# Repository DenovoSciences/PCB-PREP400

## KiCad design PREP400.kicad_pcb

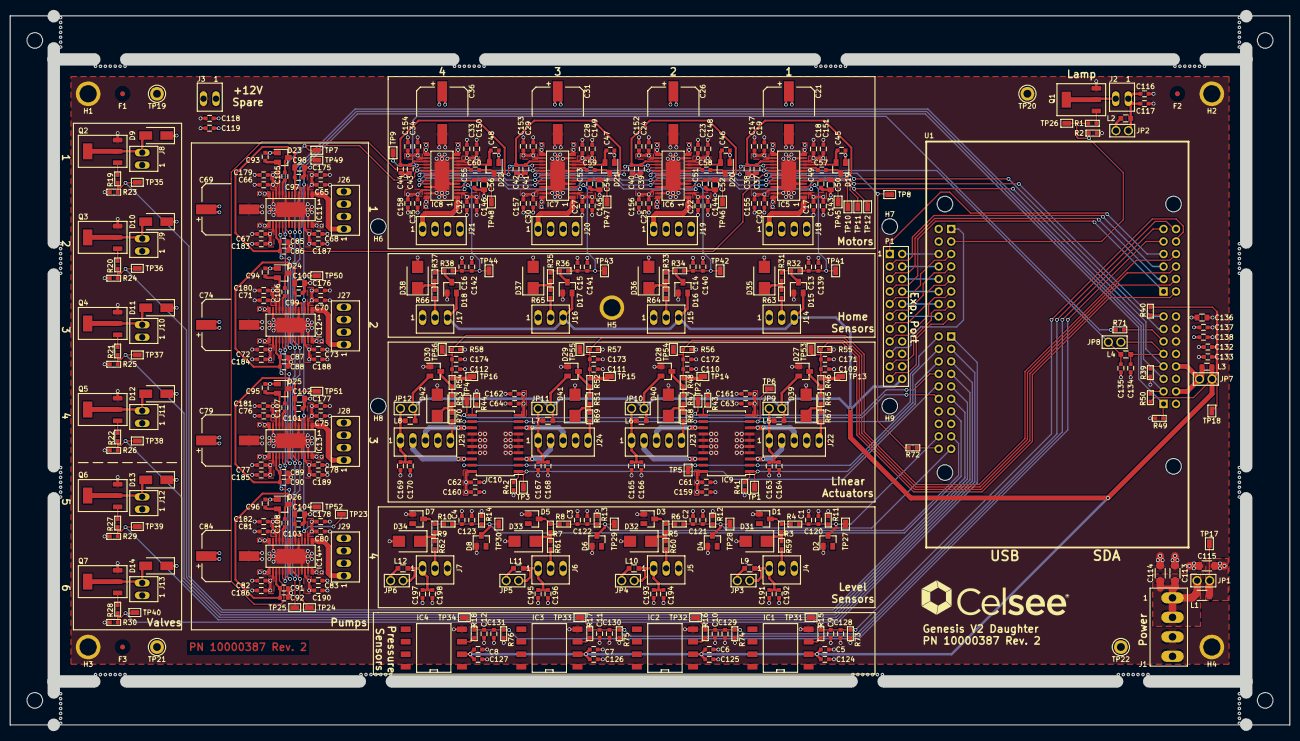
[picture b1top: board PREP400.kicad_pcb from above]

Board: 4 copper layers, 260.2 x 144.2 mm, 467 parts (0 on the bottom side), 204 nets.

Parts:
C1, C2, C3, C4, C5, C6, C7, C8, C9, C10, C11, C12, C13, C14, C15, C16, C17, C18, C19, C20, C22, C23, C24, C25, C27, C28, C29, C30, C32, C33, C34, C35, C37, C39, C41, C43, C49, C51, C53, C55, C61, C62, C63, C64, C65, C66, C67, C68, C70, C71, C72, C73, C75, C76, C77, C78, C80, C81, C82, C83, C85, C87, C89, C91, C97, C99, C101, C103, C109, C110, C111, C112, C137: 100nF/50V; CAP_SMD_0603
C21, C26, C31, C36, C69, C74, C79, C84: 100uF/50V; CAP_SMD_RAD_10MM
C38, C40, C42, C44, C86, C88, C90, C92: 10uF/6V3; CAP_SMD_0603
C45, C46, C47, C48, C93, C94, C95, C96: 220nF/50V; CAP_SMD_0603
C50, C52, C54, C56, C98, C100, C102, C104: 47uF/6V3; CAP_SMD_0805
C57, C58, C59, C60, C105, C106, C107, C108, C120, C121, C122, C123, C124, C125, C126, C127, C128, C129, C130, C131, C138, C139, C140, C141, C142, C143, C144, C145, C146, C147, C148, C149, C150, C151, C152, C153, C154, C155, C156, C157, C158, C159, C160, C161, C162, C171, C172, C173, C174, C175, C176, C177, C178, C179, C180, C181, C182, C183, C184, C185, C186, C187, C188, C189, C190: 10nF/50V; CAP_SMD_0603
C113: 100nF/50V; CAP_SMD_1206
C114: 10nF/50V; CAP_SMD_1206
C115: 1206; CAP_SMD_1206
C116, C117, C118, C119, C132, C133, C134, C135, C163, C164, C165, C166, C167, C168, C169, C170, C191, C192, C193, C194, C195, C196, C197, C198: 0603; CAP_SMD_0603
C136: 0805; CAP_SMD_0805
D1, D3, D5, D7: BAT54; SOT-23-3
D2, D4, D6, D8: BZX84; SOT-23-3
D9, D10, D11, D12, D13, D14: 100V@1A; SMA
D15, D16, D17, D18, D27, D28, D29, D30: BAT54S; SOT-23-3
D19, D20, D21, D22, D23, D24, D25, D26: BAV99; SOT-23-3
D31, D32, D33, D34, D35, D36, D37, D38, D39, D40, D41, D42: SMB
F1, F2, F3: VAL**; FID_BTM_1MM
F1#2, F2#2, F3#2: VAL**; FID_TOP_1MM
H1, H2, H3, H4, H5: VAL**; MNT_3.5MM
H6, H7, H8, H9, H10, H11, H12, H13: VAL**; MNT_0.125IN
IC1, IC2, IC3, IC4: SSC; SMT-8
IC5, IC6, IC7, IC8, IC11, IC12, IC13, IC14: L6472; HTSSOP-28
IC9, IC10: L293DD; SOIC-20
J1: MTA04-156; CON_AMP_MTA156_1x4
J2, J3, J8, J9, J10, J11, J12, J13: MTA02-100; CON_AMP_MTA100_1x2
J4, J5, J6, J7, J14, J15, J16, J17: MTA03-100; CON_AMP_MTA100_1x3
J18, J19, J20, J21, J26, J27, J28, J29: MTA04-100; CON_AMP_MTA100_1x4
J22, J23, J24, J25: MTA05-100; CON_AMP_MTA100_1x5
JP1: jump_no; CON_JMP_100_1x2
JP2, JP3, JP4, JP5, JP6, JP7, JP8, JP9, JP10, JP11, JP12: jump_nc; CON_JMP_100_1x2
L1: 1206; FER_SMD_1206
L2, L3, L4, L5, L6, L7, L8, L9, L10, L11, L12: 0805; FER_SMD_0805
P1: CONN_EXP2; CON_SAMTEC_100_2x11
Q1, Q2, Q3, Q4, Q5, Q6, Q7: FQT13N06L; SOT_223
R1, R19, R20, R21, R22, R27, R28: 330; RES_SMD_0603
R2, R23, R24, R25, R26, R29, R30, R39, R41, R42, R43, R44, R49: 10k; RES_SMD_0603
R3, R5, R7, R9, R31, R33, R35, R37, R45, R47, R51, R53, R59, R60, R61, R62, R63, R64, R65, R66, R67, R68, R69, R70: 100; RES_SMD_0603
R4, R6, R8, R10: 1.5k; RES_SMD_0603
R11, R12, R13, R14, R55, R56, R57, R58, R73, R74, R75, R76: 100k; RES_SMD_0603
R15, R16, R17, R18, R32, R34, R36, R38, R46, R48, R52, R54: 1k; RES_SMD_0603
R40, R50: 39k; RES_SMD_0603
R71, R72: 0; RES_SMD_0603
TP1, TP2, TP3, TP4, TP5, TP6, TP7, TP8, TP9, TP10, TP11, TP12, TP13, TP14, TP15, TP16, TP17, TP18, TP23, TP24, TP25, TP26, TP27, TP28, TP29, TP30, TP31, TP32, TP33, TP34, TP35, TP36, TP37, TP38, TP39, TP40, TP41, TP42, TP43, TP44, TP45, TP46, TP47, TP48, TP49, TP50, TP51, TP52, TP53, TP54, TP55, TP56: TP; TP_SMD_0603
TP19, TP20, TP21, TP22: TP; Test_Point_Keystone_5005-5009_Compact
U1: FRDM-KL25Z

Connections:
+3V3: C5.1, C6.1, C7.1, C8.1, C124.1, C125.1, C126.1, C127.1, C132.1, C133.1, D15.2, D16.2, D17.2, D18.2, D27.2, D28.2, D29.2, D30.2, IC1.2, IC2.2, IC3.2, IC4.2, J14.3, J15.3, J16.3, J17.3, JP7.2, JP9.2, JP10.2, JP11.2, JP12.2, L3.2, L5.2, L6.2, L7.2, L8.2, P1.22, R40.2, R50.2, TP18.1
+12V: C17.1, C18.1, C19.1, C20.1, C21.1, C22.1, C23.1, C24.1, C25.1, C26.1, C27.1, C28.1, C29.1, C30.1, C31.1, C32.1, C33.1, C34.1, C35.1, C36.1, C45.1, C46.1, C47.1, C48.1, C61.2, C62.2, C63.1, C64.1, C65.1, C66.1, C67.1, C68.1, C69.1, C70.1, C71.1, C72.1, C73.1, C74.1, C75.1, C76.1, C77.1, C78.1, C79.1, C80.1, C81.1, C82.1, C83.1, C84.1, C93.1, C94.1, C95.1, C96.1, C115.1, C118.1, C119.1, C136.1, C137.1, C138.1, C143.1, C144.1, C145.1, C146.1, C147.1, C148.1, C149.1, C150.1, C151.1, C152.1, C153.1, C154.1, C155.1, C156.1, C157.1, C158.1, C159.2, C160.2, C161.1, C162.1, C175.1, C176.1, C177.1, C178.1, C179.1, C180.1, C181.1, C182.1, C183.1, C184.1, C185.1, C186.1, C187.1, C188.1, C189.1, C190.1, D9.1, D10.1, D11.1, D12.1, D13.1, D14.1, D19.1, D20.1, D21.1, D22.1, D23.1, D24.1, D25.1, D26.1, IC5.2, IC5.12, IC5.16, IC5.26, IC6.2, IC6.12, IC6.16, IC6.26, IC7.2, IC7.12, IC7.16, IC7.26, IC8.2, IC8.12, IC8.16, IC8.26, IC9.10, IC9.20, IC10.10, IC10.20, IC11.2, IC11.12, IC11.16, IC11.26, IC12.2, IC12.12, IC12.16, IC12.26, IC13.2, IC13.12, IC13.16, IC13.26, IC14.2, IC14.12, IC14.16, IC14.26, J3.1, J8.1, J9.1, J10.1, J11.1, J12.1, J13.1, JP1.2, JP2.1, JP3.1, JP4.1, JP5.1, JP6.1, L1.2, L2.2, L9.1, L10.1, L11.1, L12.1, P1.14, P1.16, TP17.1, U1.4-16
/LinearActuator/LIN_OUT1A: IC9.3, J22.2
/LinearActuator/LIN_OUT1B: IC9.8, J22.3
/LinearActuator/LIN_OUT2A: IC9.18, J23.2
/LinearActuator/LIN_OUT2B: IC9.13, J23.3
/LinearActuator/LIN_OUT3A: IC10.3, J24.2
/LinearActuator/LIN_OUT3B: IC10.8, J24.3
/LinearActuator/LIN_OUT4A: IC10.18, J25.2
/LinearActuator/LIN_OUT4B: IC10.13, J25.3
/Microcontroller/EXP_A0: P1.1, U1.3-7
/Microcontroller/EXP_A1: P1.3, U1.3-5
/Microcontroller/EXP_A2: P1.5, U1.3-3
/Microcontroller/EXP_A3: P1.7, U1.3-1
/Microcontroller/EXP_D0: P1.9, U1.1-5
/Microcontroller/EXP_D1_SPI0_CS: P1.11, U1.1-7
/Microcontroller/EXP_D2_SPI0_SCK: P1.13, U1.1-9
/Microcontroller/EXP_D3_SPI0_MOSI: P1.15, U1.1-11
/Microcontroller/EXP_D4_SPI0_MISO: P1.17, U1.1-1
/Microcontroller/EXP_D5_I2C1_SCL: P1.19, U1.1-13
/Microcontroller/EXP_D6_I2C1_SDA: P1.21, U1.1-15
/Microcontroller/EXP_D7: P1.12, U1.1-16
/Microcontroller/EXP_D8: P1.10, U1.1-14
/Microcontroller/EXP_D9: P1.8, U1.1-12
/Microcontroller/EXP_D10: P1.6, U1.1-10
/Microcontroller/EXP_D11: P1.4, U1.1-8
/Microcontroller/EXP_D12: P1.2, U1.1-6
/Microcontroller/LAMP: R1.2, R2.1, TP26.1, U1.1-3
/Microcontroller/LEVEL1: C1.1, C120.1, D2.3, R4.1, R11.1, TP27.1, U1.2-18
/Microcontroller/LEVEL2: C2.1, C121.1, D4.3, R6.1, R12.1, TP28.1, U1.2-19
/Microcontroller/LEVEL3: C3.1, C122.1, D6.3, R8.1, R13.1, TP29.1, U1.2-17
/Microcontroller/LEVEL4: C4.1, C123.1, D8.3, R10.1, R14.1, TP30.1, U1.2-13
/Microcontroller/LIN_ACT_DIR: IC9.2, IC9.19, IC10.2, IC10.19, TP5.1, U1.2-4
/Microcontroller/LIN_ACT_EN1: IC9.1, R41.1, TP1.1, U1.2-6
/Microcontroller/LIN_ACT_EN2: IC9.11, R43.2, TP2.1, U1.2-8
/Microcontroller/LIN_ACT_EN3: IC10.1, R42.1, TP3.1, U1.2-10
/Microcontroller/LIN_ACT_EN4: IC10.11, R44.2, TP4.1, U1.2-12
/Microcontroller/LIN_ACT_POS1: C109.1, C171.1, R46.2, R55.1, TP13.1, TP53.1, U1.3-2
/Microcontroller/LIN_ACT_POS2: C110.1, C172.1, R48.2, R56.1, TP14.1, TP54.1, U1.3-4
/Microcontroller/LIN_ACT_POS3: C111.1, C173.1, R52.2, R57.1, TP15.1, TP55.1, U1.3-6
/Microcontroller/LIN_ACT_POS4: C112.1, C174.1, R54.2, R58.1, TP16.1, TP56.1, U1.3-8
/Microcontroller/PRESSURE1: C9.1, C128.1, R15.1, R73.1, TP31.1, U1.3-10
/Microcontroller/PRESSURE2: C10.1, C129.1, R16.1, R74.1, TP32.1, U1.3-12
/Microcontroller/PRESSURE3: C11.1, C130.1, R17.1, R75.1, TP33.1, U1.3-11
/Microcontroller/PRESSURE4: C12.1, C131.1, R18.1, R76.1, TP34.1, U1.3-9
/Microcontroller/VALVE1: R19.2, R23.1, TP35.1, U1.2-11
/Microcontroller/VALVE2: R20.2, R24.1, TP36.1, U1.2-9
/Microcontroller/VALVE3: R21.2, R25.1, TP37.1, U1.2-7
/Microcontroller/VALVE4: R22.2, R26.1, TP38.1, U1.2-5
/Microcontroller/VALVE5: R27.2, R29.1, TP39.1, U1.2-3
/Microcontroller/VALVE6: R28.2, R30.1, TP40.1, U1.2-1
/Microcontroller/_LIN_ACT_DIR: IC9.9, IC9.12, IC10.9, IC10.12, TP6.1, U1.2-2
/Motor/MOT1_1A: IC5.1, J18.1
/Motor/MOT1_1B: IC5.14, J18.4
/Motor/MOT1_2A: IC5.28, J18.2
/Motor/MOT1_2B: IC5.15, J18.3
/Motor/MOT1_HOME: C13.1, C139.1, IC5.4, R32.2, TP41.1
/Motor/MOT2_1A: IC6.1, J19.1
/Motor/MOT2_1B: IC6.14, J19.4
/Motor/MOT2_2A: IC6.28, J19.2
/Motor/MOT2_2B: IC6.15, J19.3
/Motor/MOT2_HOME: C14.1, C140.1, IC6.4, R34.2, TP42.1
/Motor/MOT3_1A: IC7.1, J20.1
/Motor/MOT3_1B: IC7.14, J20.4
/Motor/MOT3_2A: IC7.28, J20.2
/Motor/MOT3_2B: IC7.15, J20.3
/Motor/MOT3_HOME: C15.1, C141.1, IC7.4, R36.2, TP43.1
/Motor/MOT4_1A: IC8.1, J21.1
/Motor/MOT4_1B: IC8.14, J21.4
/Motor/MOT4_2A: IC8.28, J21.2
/Motor/MOT4_2B: IC8.15, J21.3
/Motor/MOT4_HOME: C16.1, C142.1, IC8.4, R38.2, TP44.1
/Motor/MOT_SCK: C135.1, IC5.19, IC6.19, IC7.19, IC8.19, IC11.19, IC12.19, IC13.19, IC14.19, JP8.2, L4.2, TP7.1
/Motor/MOT_SDI: IC5.20, IC11.20, R72.2, TP8.1
/Motor/MOT_SDO: IC8.18, IC14.18, R71.1, TP9.1
/Motor/_MOTC_CS: IC5.23, IC6.23, IC7.23, IC8.23, TP10.1, U1.4-13
/Motor/_MOTC_FLG: IC5.24, IC6.24, IC7.24, IC8.24, R40.1, TP11.1, U1.4-15
/Motor/_MOTC_RST: IC5.3, IC6.3, IC7.3, IC8.3, R39.2, TP12.1, U1.4-7
/Pump/MOT1_1A: IC11.1, J26.1
/Pump/MOT1_1B: IC11.14, J26.4
/Pump/MOT1_2A: IC11.28, J26.2
/Pump/MOT1_2B: IC11.15, J26.3
/Pump/MOT1_VDD: C85.1, C86.1, C97.1, C98.1, IC11.4, IC11.6, IC11.17, TP49.1
/Pump/MOT2_1A: IC12.1, J27.1
/Pump/MOT2_1B: IC12.14, J27.4
/Pump/MOT2_2A: IC12.28, J27.2
/Pump/MOT2_2B: IC12.15, J27.3
/Pump/MOT2_VDD: C87.1, C88.1, C99.1, C100.1, IC12.4, IC12.6, IC12.17, TP50.1
/Pump/MOT3_1A: IC13.1, J28.1
/Pump/MOT3_1B: IC13.14, J28.4
/Pump/MOT3_2A: IC13.28, J28.2
/Pump/MOT3_2B: IC13.15, J28.3
/Pump/MOT3_VDD: C89.1, C90.1, C101.1, C102.1, IC13.4, IC13.6, IC13.17, TP51.1
/Pump/MOT4_1A: IC14.1, J29.1
/Pump/MOT4_1B: IC14.14, J29.4
/Pump/MOT4_2A: IC14.28, J29.2
/Pump/MOT4_2B: IC14.15, J29.3
/Pump/MOT4_VDD: C91.1, C92.1, C103.1, C104.1, IC14.4, IC14.6, IC14.17, TP52.1
/Pump/_MOTP_CS: IC11.23, IC12.23, IC13.23, IC14.23, TP25.1, U1.4-5
/Pump/_MOTP_FLG: IC11.24, IC12.24, IC13.24, IC14.24, R50.1, TP24.1, U1.4-3
/Pump/_MOTP_RST: IC11.3, IC12.3, IC13.3, IC14.3, R49.2, TP23.1, U1.4-1
GND: C1.2, C2.2, C3.2, C4.2, C5.2, C6.2, C7.2, C8.2, C9.2, C10.2, C11.2, C12.2, C13.2, C14.2, C15.2, C16.2, C17.2, C18.2, C19.2, C20.2, C21.2, C22.2, C23.2, C24.2, C25.2, C26.2, C27.2, C28.2, C29.2, C30.2, C31.2, C32.2, C33.2, C34.2, C35.2, C36.2, C37.2, C38.2, C39.2, C40.2, C41.2, C42.2, C43.2, C44.2, C49.2, C50.2, C51.2, C52.2, C53.2, C54.2, C55.2, C56.2, C61.1, C62.1, C63.2, C64.2, C65.2, C66.2, C67.2, C68.2, C69.2, C70.2, C71.2, C72.2, C73.2, C74.2, C75.2, C76.2, C77.2, C78.2, C79.2, C80.2, C81.2, C82.2, C83.2, C84.2, C85.2, C86.2, C87.2, C88.2, C89.2, C90.2, C91.2, C92.2, C97.2, C98.2, C99.2, C100.2, C101.2, C102.2, C103.2, C104.2, C109.2, C110.2, C111.2, C112.2, C113.2, C114.2, C115.2, C116.2, C117.2, C118.2, C119.2, C120.2, C121.2, C122.2, C123.2, C124.2, C125.2, C126.2, C127.2, C128.2, C129.2, C130.2, C131.2, C132.2, C133.2, C134.2, C135.2, C136.2, C137.2, C138.2, C139.2, C140.2, C141.2, C142.2, C143.2, C144.2, C145.2, C146.2, C147.2, C148.2, C149.2, C150.2, C151.2, C152.2, C153.2, C154.2, C155.2, C156.2, C157.2, C158.2, C159.1, C160.1, C161.2, C162.2, C163.1, C164.1, C165.1, C166.1, C167.1, C168.1, C169.1, C170.1, C171.2, C172.2, C173.2, C174.2, C175.2, C176.2, C177.2, C178.2, C179.2, C180.2, C181.2, C182.2, C183.2, C184.2, C185.2, C186.2, C187.2, C188.2, C189.2, C190.2, C191.1, C192.1, C193.1, C194.1, C195.1, C196.1, C197.1, C198.1, D1.1, D2.1, D3.1, D4.1, D5.1, D6.1, D7.1, D8.1, D15.1, D16.1, D17.1, D18.1, D27.1, D28.1, D29.1, D30.1, D31.2, D32.2, D33.2, D34.2, D35.2, D36.2, D37.2, D38.2, D39.2, D40.2, D41.2, D42.2, H1.1, H2.1, H3.1, H4.1, H5.1, IC1.4, IC2.4, IC3.4, IC4.4, IC5.5, IC5.9, IC5.13, IC5.21, IC5.25, IC5.27, IC5.29, IC6.5, IC6.9, IC6.13, IC6.21, IC6.25, IC6.27, IC6.29, IC7.5, IC7.9, IC7.13, IC7.21, IC7.25, IC7.27, IC7.29, IC8.5, IC8.9, IC8.13, IC8.21, IC8.25, IC8.27, IC8.29, IC9.4, IC9.5, IC9.6, IC9.7, IC9.14, IC9.15, IC9.16, IC9.17, IC10.4, IC10.5, IC10.6, IC10.7, IC10.14, IC10.15, IC10.16, IC10.17, IC11.5, IC11.9, IC11.13, IC11.21, IC11.25, IC11.27, IC11.29, IC12.5, IC12.9, IC12.13, IC12.21, IC12.25, IC12.27, IC12.29, IC13.5, IC13.9, IC13.13, IC13.21, IC13.25, IC13.27, IC13.29, IC14.5, IC14.9, IC14.13, IC14.21, IC14.25, IC14.27, IC14.29, J1.3, J1.4, J3.2, J4.3, J5.3, J6.3, J7.3, J14.1, J15.1, J16.1, J17.1, J22.4, J23.4, J24.4, J25.4, P1.18, P1.20, Q1.S, Q2.S, Q3.S, Q4.S, Q5.S, Q6.S, Q7.S, R2.2, R11.2, R12.2, R13.2, R14.2, R23.2, R24.2, R25.2, R26.2, R29.2, R30.2, R39.1, R41.2, R42.2, R43.1, R44.1, R49.1, R55.2, R56.2, R57.2, R58.2, R73.2, R74.2, R75.2, R76.2, TP19.1, TP20.1, TP21.1, TP22.1, U1.2-14, U1.4-12, U1.4-14
unnamed: C37.1, C38.1, C49.1, C50.1, IC5.6, IC5.17, TP45.1
unnamed: C39.1, C40.1, C51.1, C52.1, IC6.6, IC6.17, TP46.1
unnamed: C41.1, C42.1, C53.1, C54.1, IC7.6, IC7.17, TP47.1
unnamed: C43.1, C44.1, C55.1, C56.1, IC8.6, IC8.17, TP48.1
unnamed: C45.2, D19.2, IC5.11
unnamed: C46.2, D20.2, IC6.11
unnamed: C47.2, D21.2, IC7.11
unnamed: C48.2, D22.2, IC8.11
unnamed: C57.1, D19.3
unnamed: C57.2, IC5.10
unnamed: C58.1, D20.3
unnamed: C58.2, IC6.10
unnamed: C59.1, D21.3
unnamed: C59.2, IC7.10
unnamed: C60.1, D22.3
unnamed: C60.2, IC8.10
unnamed: C93.2, D23.2, IC11.11
unnamed: C94.2, D24.2, IC12.11
unnamed: C95.2, D25.2, IC13.11
unnamed: C96.2, D26.2, IC14.11
unnamed: C105.1, D23.3
unnamed: C105.2, IC11.10
unnamed: C106.1, D24.3
unnamed: C106.2, IC12.10
unnamed: C107.1, D25.3
unnamed: C107.2, IC13.10
unnamed: C108.1, D26.3
unnamed: C108.2, IC14.10
unnamed: C113.1, C114.1, J1.1, J1.2, JP1.1, L1.1
unnamed: C116.1, C117.1, J2.1, JP2.2, L2.1
unnamed: C134.1, JP8.1, L4.1, U1.4-9
unnamed: C163.2, C164.2, J22.1, JP9.1, L5.1
unnamed: C165.2, C166.2, J23.1, JP10.1, L6.1
unnamed: C167.2, C168.2, J24.1, JP11.1, L7.1
unnamed: C169.2, C170.2, J25.1, JP12.1, L8.1
unnamed: C191.2, C192.2, J4.1, JP3.2, L9.2
unnamed: C193.2, C194.2, J5.1, JP4.2, L10.2
unnamed: C195.2, C196.2, J6.1, JP5.2, L11.2
unnamed: C197.2, C198.2, J7.1, JP6.2, L12.2
unnamed: D1.3, R3.1, R4.2
unnamed: D3.3, R5.1, R6.2
unnamed: D5.3, R7.1, R8.2
unnamed: D7.3, R9.1, R10.2
unnamed: D9.2, J8.2, Q2.D
unnamed: D10.2, J9.2, Q3.D
unnamed: D11.2, J10.2, Q4.D
unnamed: D12.2, J11.2, Q5.D
unnamed: D13.2, J12.2, Q6.D
unnamed: D14.2, J13.2, Q7.D
unnamed: D15.3, R31.2, R32.1
unnamed: D16.3, R33.2, R34.1
unnamed: D17.3, R35.2, R36.1
unnamed: D18.3, R37.2, R38.1
unnamed: D27.3, R45.2, R46.1
unnamed: D28.3, R47.2, R48.1
unnamed: D29.3, R51.2, R52.1
unnamed: D30.3, R53.2, R54.1
unnamed: D31.1, R3.2, R59.1
unnamed: D32.1, R5.2, R60.1
unnamed: D33.1, R7.2, R61.1
unnamed: D34.1, R9.2, R62.1
unnamed: D35.1, R31.1, R63.2
unnamed: D36.1, R33.1, R64.2
unnamed: D37.1, R35.1, R65.2
unnamed: D38.1, R37.1, R66.2
unnamed: D39.1, R45.1, R67.2
unnamed: D40.1, R47.1, R68.2
unnamed: D41.1, R51.1, R69.2
unnamed: D42.1, R53.1, R70.2
unnamed: IC1.3, R15.2
unnamed: IC2.3, R16.2
unnamed: IC3.3, R17.2
unnamed: IC4.3, R18.2
unnamed: IC5.18, IC6.20
unnamed: IC6.18, IC7.20
unnamed: IC7.18, IC8.20
unnamed: IC11.18, IC12.20
unnamed: IC12.18, IC13.20
unnamed: IC13.18, IC14.20
unnamed: J2.2, Q1.D
unnamed: J4.2, R59.2
unnamed: J5.2, R60.2
unnamed: J6.2, R61.2
unnamed: J7.2, R62.2
unnamed: J14.2, R63.1
unnamed: J15.2, R64.1
unnamed: J16.2, R65.1
unnamed: J17.2, R66.1
unnamed: J22.5, R67.1
unnamed: J23.5, R68.1
unnamed: J24.5, R69.1
unnamed: J25.5, R70.1
unnamed: JP7.1, L3.1, U1.4-4, U1.4-8
unnamed: Q1.G, R1.1
unnamed: Q2.G, R19.1
unnamed: Q3.G, R20.1
unnamed: Q4.G, R21.1
unnamed: Q5.G, R22.1
unnamed: Q6.G, R27.1
unnamed: Q7.G, R28.1
unnamed: R71.2, U1.4-11
unnamed: R72.1, U1.2-20

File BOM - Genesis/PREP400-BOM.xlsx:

References | Quantity | Description | Mfg | MfgPartNum | DigikeyPartNum | AltDigikeyPartNum | Notes
C1, C2, C3, C4, C5, C6, C7, C8, C9, C10, C11, C12, C13, C14, C15, C16, C17, C18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 | 84 | CAP CER 0.1UF 50V X7R 0603 | Murata | GCM188R71H104KA57J | 490-8020-1-ND |  | Do Not Populate: C116, C132, C163, C165, C167, C169, C191, C193, C195, C197
C113 | 1 | CAP CER 0.1UF 100V X7R 1206 | Kemet | C1206C104K1RACAUTO | 399-7008-1-ND | 445-5840-1-ND | Do Not Populate: C113
C21, C26, C31, C36, C69, C74, C79, C84 | 8 | CAP ALUM POLY 100UF 20% 50V SMD | Panasonic | EEH-ZC1H101V | P19837CT-ND | 50PFV100M10X10.5CT-ND
C38, C40, C42, C44, C86, C88, C90, C92 | 8 | CAP CER 10UF 10V X5R 0603 | TDK | C1608X5R1A106K080AC | 445-7486-1-ND | 1276-1038-1-ND
C45, C46, C47, C48, C93, C94, C95, C96 | 8 | CAP CER 0.22UF 50V X7R 0603 | Samsung | CL10B224KB8VPNC | 1276-6600-1-ND
C50, C52, C54, C56, C98, C100, C102, C104, C136 | 9 | CAP CER 47UF 6.3V X5R 0805 | Samsung | CL21A476MQ9LRNC | 1276-2419-1-ND |  | Do Not Populate: C136
C115 | 1 | CAP CER 47UF 6.3V X5R 1206 | Samsung | CL31A476KQHNNNE | 1276-3062-1-ND |  | Do Not Populate: C115
C57, C58, C59, C60, C105, C106, C107, C108, C117, C119, C120, C121, C122, C123,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 | 77 | CAP CER 10000PF 50V X7R 0603 | Murata | GCM188R71H103KA37D | 490-4778-1-ND |  | Do Not Populate: C117, C133, C134, C164, C166, C168, C170, C192, C194, C196, C1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
C114 | 1 | CAP CER 10000PF 200V X7R 1206 | AVX | 12062C103K4T2A | 478-9898-1-ND |  | Do Not Populate: C114
C135 | 1 | CAP CER 10PF 50V C0G/NP0 0603 | Samsung | CL10C100JB81PNC | 1276-2153-1-ND |  | Do Not Populate: C135
D1, D3, D5, D7 | 4 | DIODE SCHOTTKY 30V 200MA SOT23-3 | Diodes Inc. | BAT54 | BAT54-FDICT-ND | BAT54E6327HTSA1 | BAT54FSCT-ND end of life
D2, D4, D6, D8 | 4 | DIODE ZENER 3.3V 350MW SOT23-3 | Micro Commercial | BZX84C3V3 | BZX84C3V3-TPMSCT-ND |  | BZX84C3V3FSCT-ND obsolete
D9, D10, D11, D12, D13, D14 | 6 | DIODE GEN PURP 100V 1A SMA | ON Semi | ES1B | ES1BFSCT-ND | CD214A-F1100CT-ND
D15, D16, D17, D18, D27, D28, D29, D30 | 8 | DIODE ARRAY SCHOTTKY 30V SOT23-3 | ON Semi | BAT54S | BAT54SLT1GOSCT-ND |  | BAT54SFSCT-ND end of life
D19, D20, D21, D22, D23, D24, D25, D26 | 8 | DIODE ARRAY GP 70V 200MA SOT23-3 | Taiwan Semi | BAV99 | BAV99RFGCT-ND |  | BAV99FSCT-ND end of life
D31, D32, D33, D34, D35, D36, D37, D38, D39, D40, D41, D42 | 12 | TVS DIODE 12V 19V SMB | Littlefuse | SACB12 | SACB12CT-ND | SMBJ12ABCT-ND
IC1, IC2, IC3, IC4 | 4 | SENSOR PRES 160M DIFF 3.3V SMD | Honeywell | SSCMRRN160MDAA3 | 480-6445-ND |  | 480-5530-ND is possible alternate at 5psi but would require firmware update.
IC5, IC6, IC7, IC8, IC11, IC12, IC13, IC14 | 8 | IC MOTOR DRIVER SPI 28HTSSOP | STMicro | L6472H | 497-14690-5-ND | 497-14775-5-ND
IC9, IC10 | 2 | IC MOTOR DRIVER PAR 20-SOIC | STMicro | L293DD | 497-1390-5-ND | 497-2937-1-ND
J1 | 1 | CONN HEADER 4POS VERT .156 GOLD | TE | 3-641209-4 | A105038-ND | WM5226-ND
J2, J3, J8, J9, J10, J11, J12, J13 | 8 | CONN HEADER VERT 2POS .100 30AU | TE | 3-641215-2 | A30786-ND | WM2700-ND
J4, J5, J6, J7, J14, J15, J16, J17 | 8 | CONN HEADER VERT 3POS .100 30AU | TE | 3-641215-3 | A30787-ND | WM2701-ND
J18, J19, J20, J21, J26, J27, J28, J29 | 8 | CONN HEADER VERT 4POS .100 30AU | TE | 3-641215-4 | A30788-ND | WM2746-ND
J22, J23, J24, J25 | 4 | CONN HEADER VERT 5POS .100 30AU | TE | 3-641215-5 | A30789-ND | WM2703-ND
JP1, JP2, JP3, JP4, JP5, JP6, JP7, JP8, JP9, JP10, JP11, JP12 | 12 | CONN HEADER 2POS .100" SNGL | Samtec | TSW-102-07-F-S | SAM10844-ND | SAM1031-02-ND | Jumper Header
 | 12 | CONN JUMPER SHORTING GOLD FLASH | Sullins | QPC02SXGN-RC | S9337-ND | S9001-ND | Jumper - populate on header
L1 | 1 | FERRITE BEAD 50 OHM 1206 1LN | Murata | BLM31SN500SH1L | 490-13268-1-ND | 490-13270-1-ND | Do Not Populate: L1
L2, L3, L4, L5, L6, L7, L8, L9, L10, L11, L12 | 11 | FERRITE BEAD 1 KOHM 0805 1LN | TDK | MPZ2012S102ATD25 | 445-172904-1-ND | 445-5223-1-ND | Do Not Populate: L2, L3, L4, L5, L6, L7, L8, L9, L10, L11, L12
P1 | 1 | .025" BOARD SPACERS | Samtec | DW-11-11-F-D-665 | DW-11-11-F-D-665-ND |  | Not stocked. Long lead time component.
Q1, Q2, Q3, Q4, Q5, Q6, Q7 | 7 | MOSFET N-CH 60V 2.8A SOT-223 | ON Semi | FQT13N06LTF | FQT13N06LTFCT-ND
R1, R19, R20, R21, R22, R27, R28 | 7 | RES SMD 330 OHM 1% 1/10W 0603 | Samsung | RC1608F331CS | 1276-4604-1-ND | CR0603-FX-3300ELFCT-ND
R2, R23, R24, R25, R26, R29, R30, R39, R41, R42, R43, R44, R49 | 13 | RES SMD 10K OHM 1% 1/10W 0603 | Panasonic | ERJ-3EKF1002V | P10.0KHCT-ND
R3, R5, R7, R9, R31, R33, R35, R37, R45, R47, R51, R53, R59, R60, R61, R62, R63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 | 24 | RES SMD 100 OHM 1% 1/10W 0603 | Panasonic | ERJ-3EKF1000V | P100HCT-ND
R4, R6, R8, R10 | 4 | RES SMD 1.5K OHM 1% 1/10W 0603 | Samsung | RC1608F152CS | 1276-4660-1-ND | CR0603-FX-1501ELFCT-ND
R11, R12, R13, R14, R55, R56, R57, R58, R73, R74, R75, R76 | 12 | RES SMD 100K OHM 1% 1/10W 0603 | Panasonic | ERJ-3EKF1003V | P100KHCT-ND
R15, R16, R17, R18, R32, R34, R36, R38, R46, R48, R52, R54 | 12 | RES SMD 1K OHM 1% 1/10W 0603 | Panasonic | RC1608F102CS | P1.00KHCT-ND
R40, R50 | 2 | RES SMD 39K OHM 1% 1/10W 0603 | Panasonic | RC0603FR-0739KL | P39.0KHCT-ND
R71, R72 | 2 | RES SMD 0 OHM JUMPER 1/10W 0603 | Panasonic | ERJ-3GEY0R00V | P0.0GCT-ND | RMCF0603ZT0R00CT-ND
TP1, TP2, TP3, TP4, TP5, TP6, TP7, TP8, TP9, TP10, TP11, TP12, TP13, TP14, TP15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 | 52 | PC TEST POINT TIN SMD | Harwin | S2761-46R | 952-2665-1-ND | A106145CT-ND
TP19, TP20, TP21, TP22 | 4 | TEST POINT PC COMPACT .063"D BLK | Keystone | 5006 | 36-5006-ND | 36-5123-ND
U1 | 1 | CONN HEADER FMAL 12PS.1" DL GOLD | Sullins | PPPC062LFBN-RC | S7109-ND | S7074-ND | Goes to 12 position header of U1 (Mate: 609-3213-ND)
 | 2 | CONN HEADER FMAL 16PS.1" DL GOLD | Sullins | PPPC082LFBN-RC | S7111-ND | S7076-ND | Goes to 16 position headers of U1 (Mate: 609-3389-ND)
 | 1 | CONN HEADER FEM 20POS.1" DL GOLD | Sullins | PPPC102LFBN-RC | S6106-ND | S7078-ND | Goes to 20 position header of U1 (Mate: 609-3214-ND)
 | 1 | FREEDOM BOARD KINETIS L | NXP | FRDM-KL25Z | FRDM-KL25Z-ND |  | Motherboard. Remove D8, D11 from FRDM-KL25Z
 | 1 | CONN HEADER 12POS .100 STR 15AU | Amphenol | 67996-212HLF | 609-3213-ND | 609-3204-ND, 609-3219-ND | Goes to J10 of FRDM-KL25Z
 | 2 | CONN HEADER 16POS .100 STR 15AU | Amphenol | 67996-216HLF | 609-3389-ND | 609-3205-ND, 609-3220-ND | Goes to J1, J9 of FRDM-KL25Z
 | 1 | CONN HEADER 20POS .100 STR 15AU | Amphenol | 67996-220HLF | 609-3214-ND | 609-3206-ND, 609-3221-ND | Goes to J2 of FRDM-KL25Z

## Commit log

2018-06-06 Initial release of PREP400 PCB
2018-06-06 Scrubbed BOM for obsolete parts
2018-06-06 Added expansion connector for Genesis Aux PCB
2018-06-07 Added Celsee part numbers
2018-10-01 Scrubbed BOM
2018-10-01 Added Gronk Daughter BOM
2018-10-05 Added Celsee part numbers.
2018-10-18 Added fab drawing for assembly
2018-10-23 Added revision column. Updated manufacturer part numbers.
2018-10-25 Added part numbers
2018-10-31 Updated pressure sensor
2018-11-13 Fixed component typos
2018-11-28 Paramit release
2019-01-25 Add new BOM format
2019-04-02 Address DFM from Paramit
2019-04-05 WIP add RoHS Certs
